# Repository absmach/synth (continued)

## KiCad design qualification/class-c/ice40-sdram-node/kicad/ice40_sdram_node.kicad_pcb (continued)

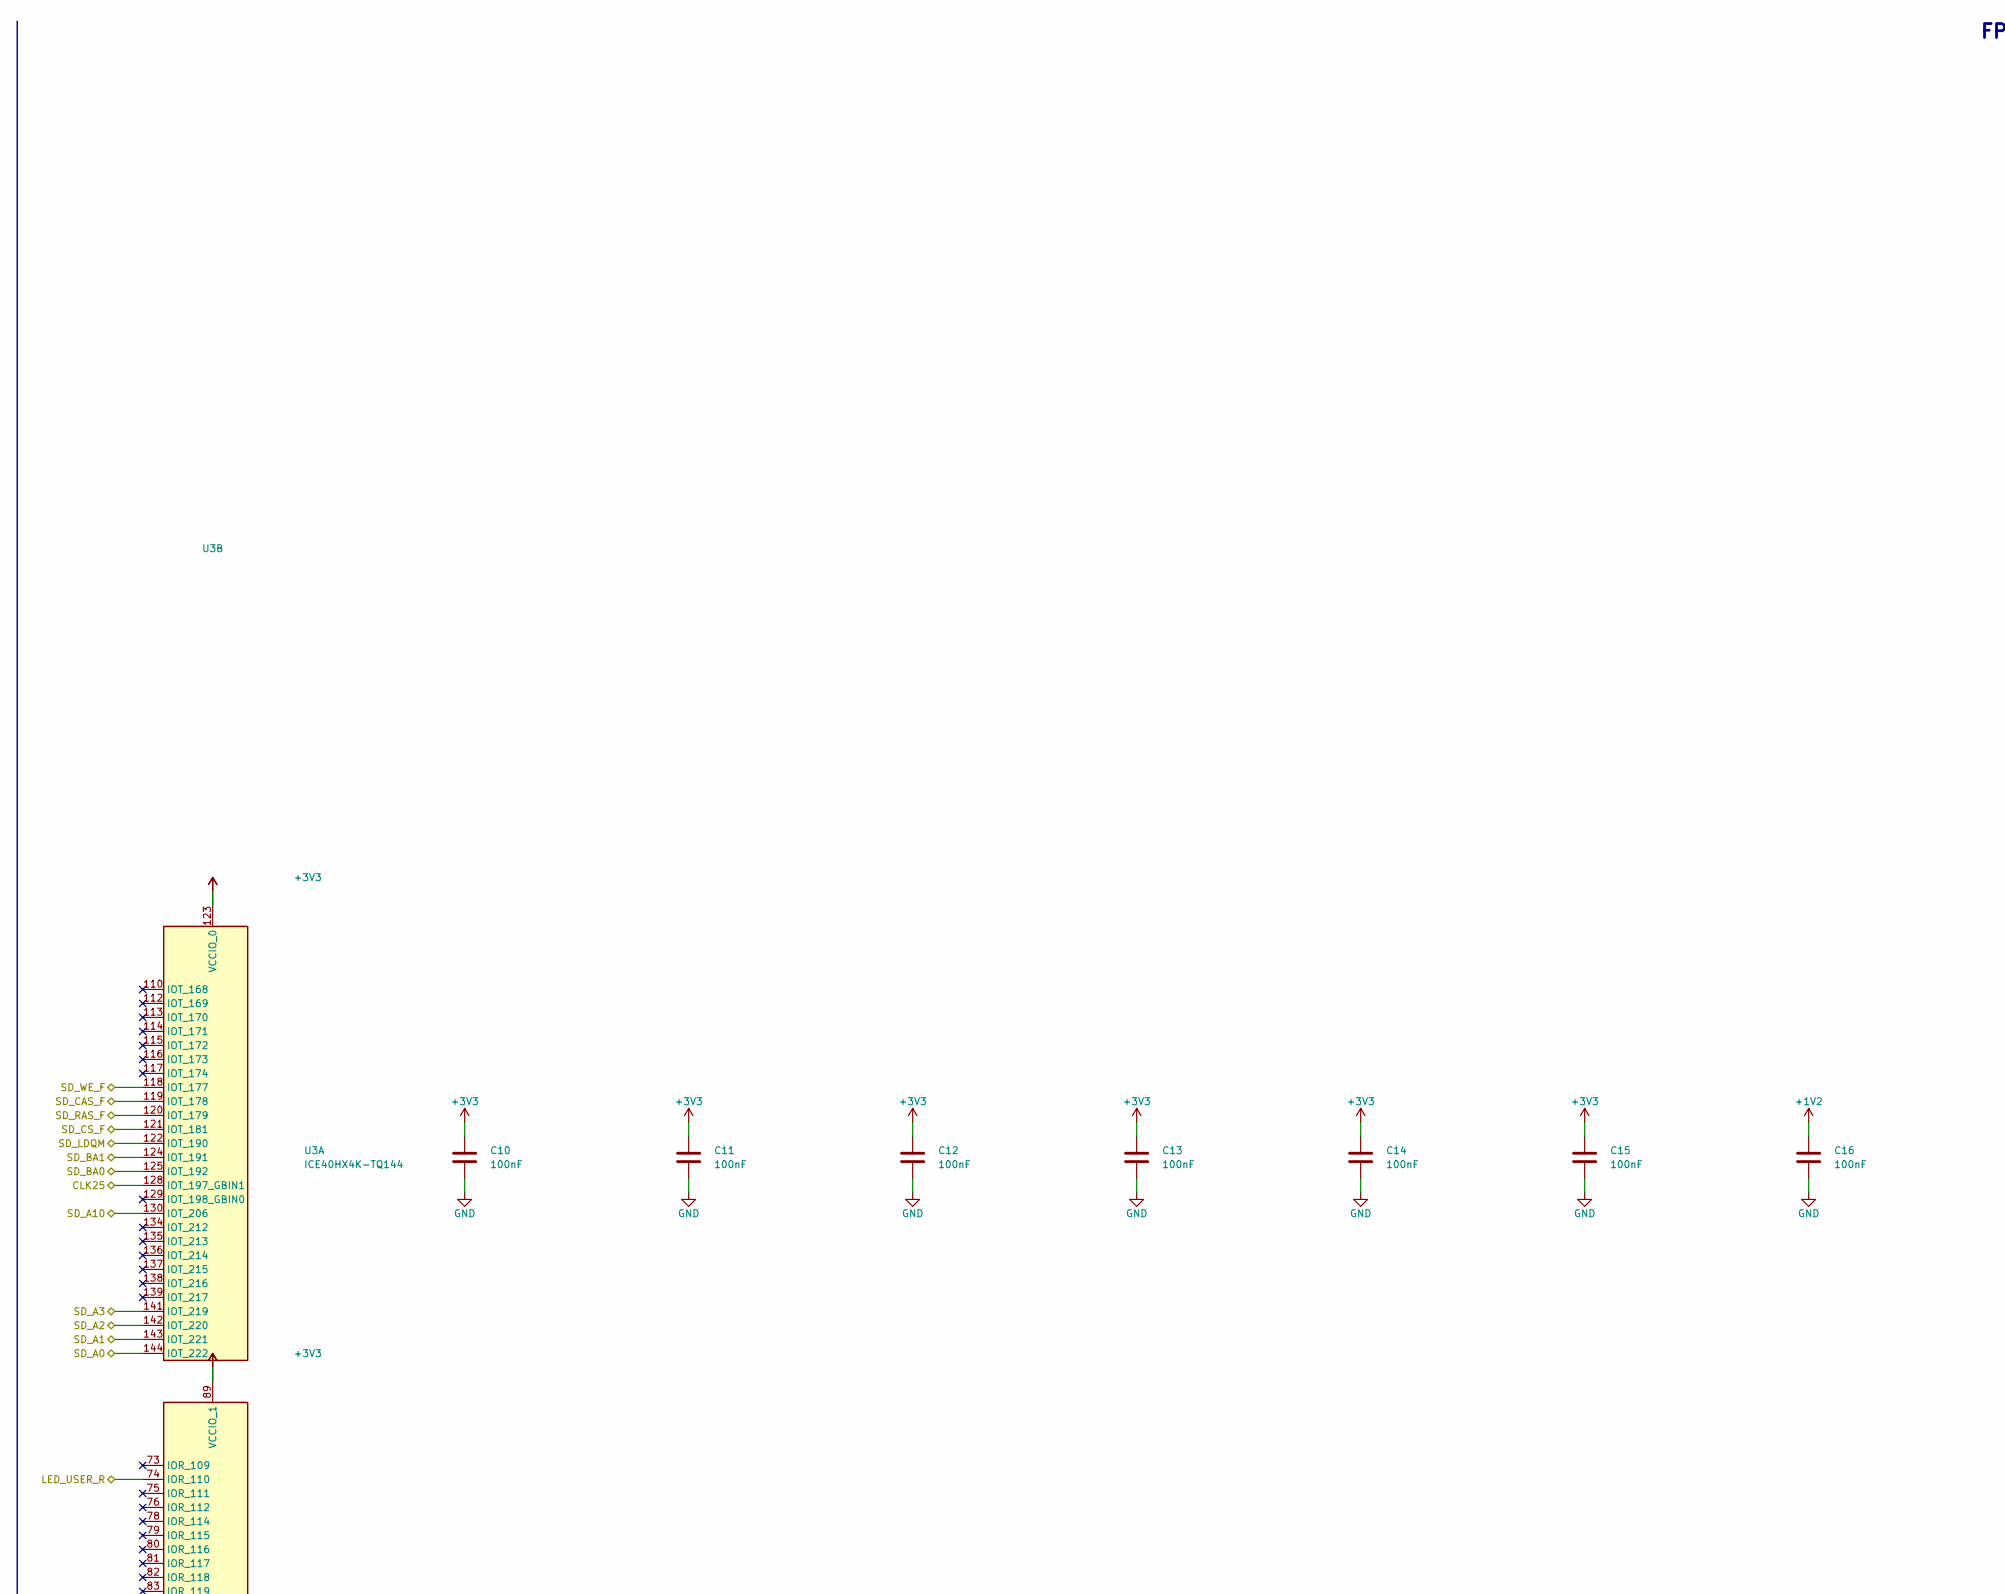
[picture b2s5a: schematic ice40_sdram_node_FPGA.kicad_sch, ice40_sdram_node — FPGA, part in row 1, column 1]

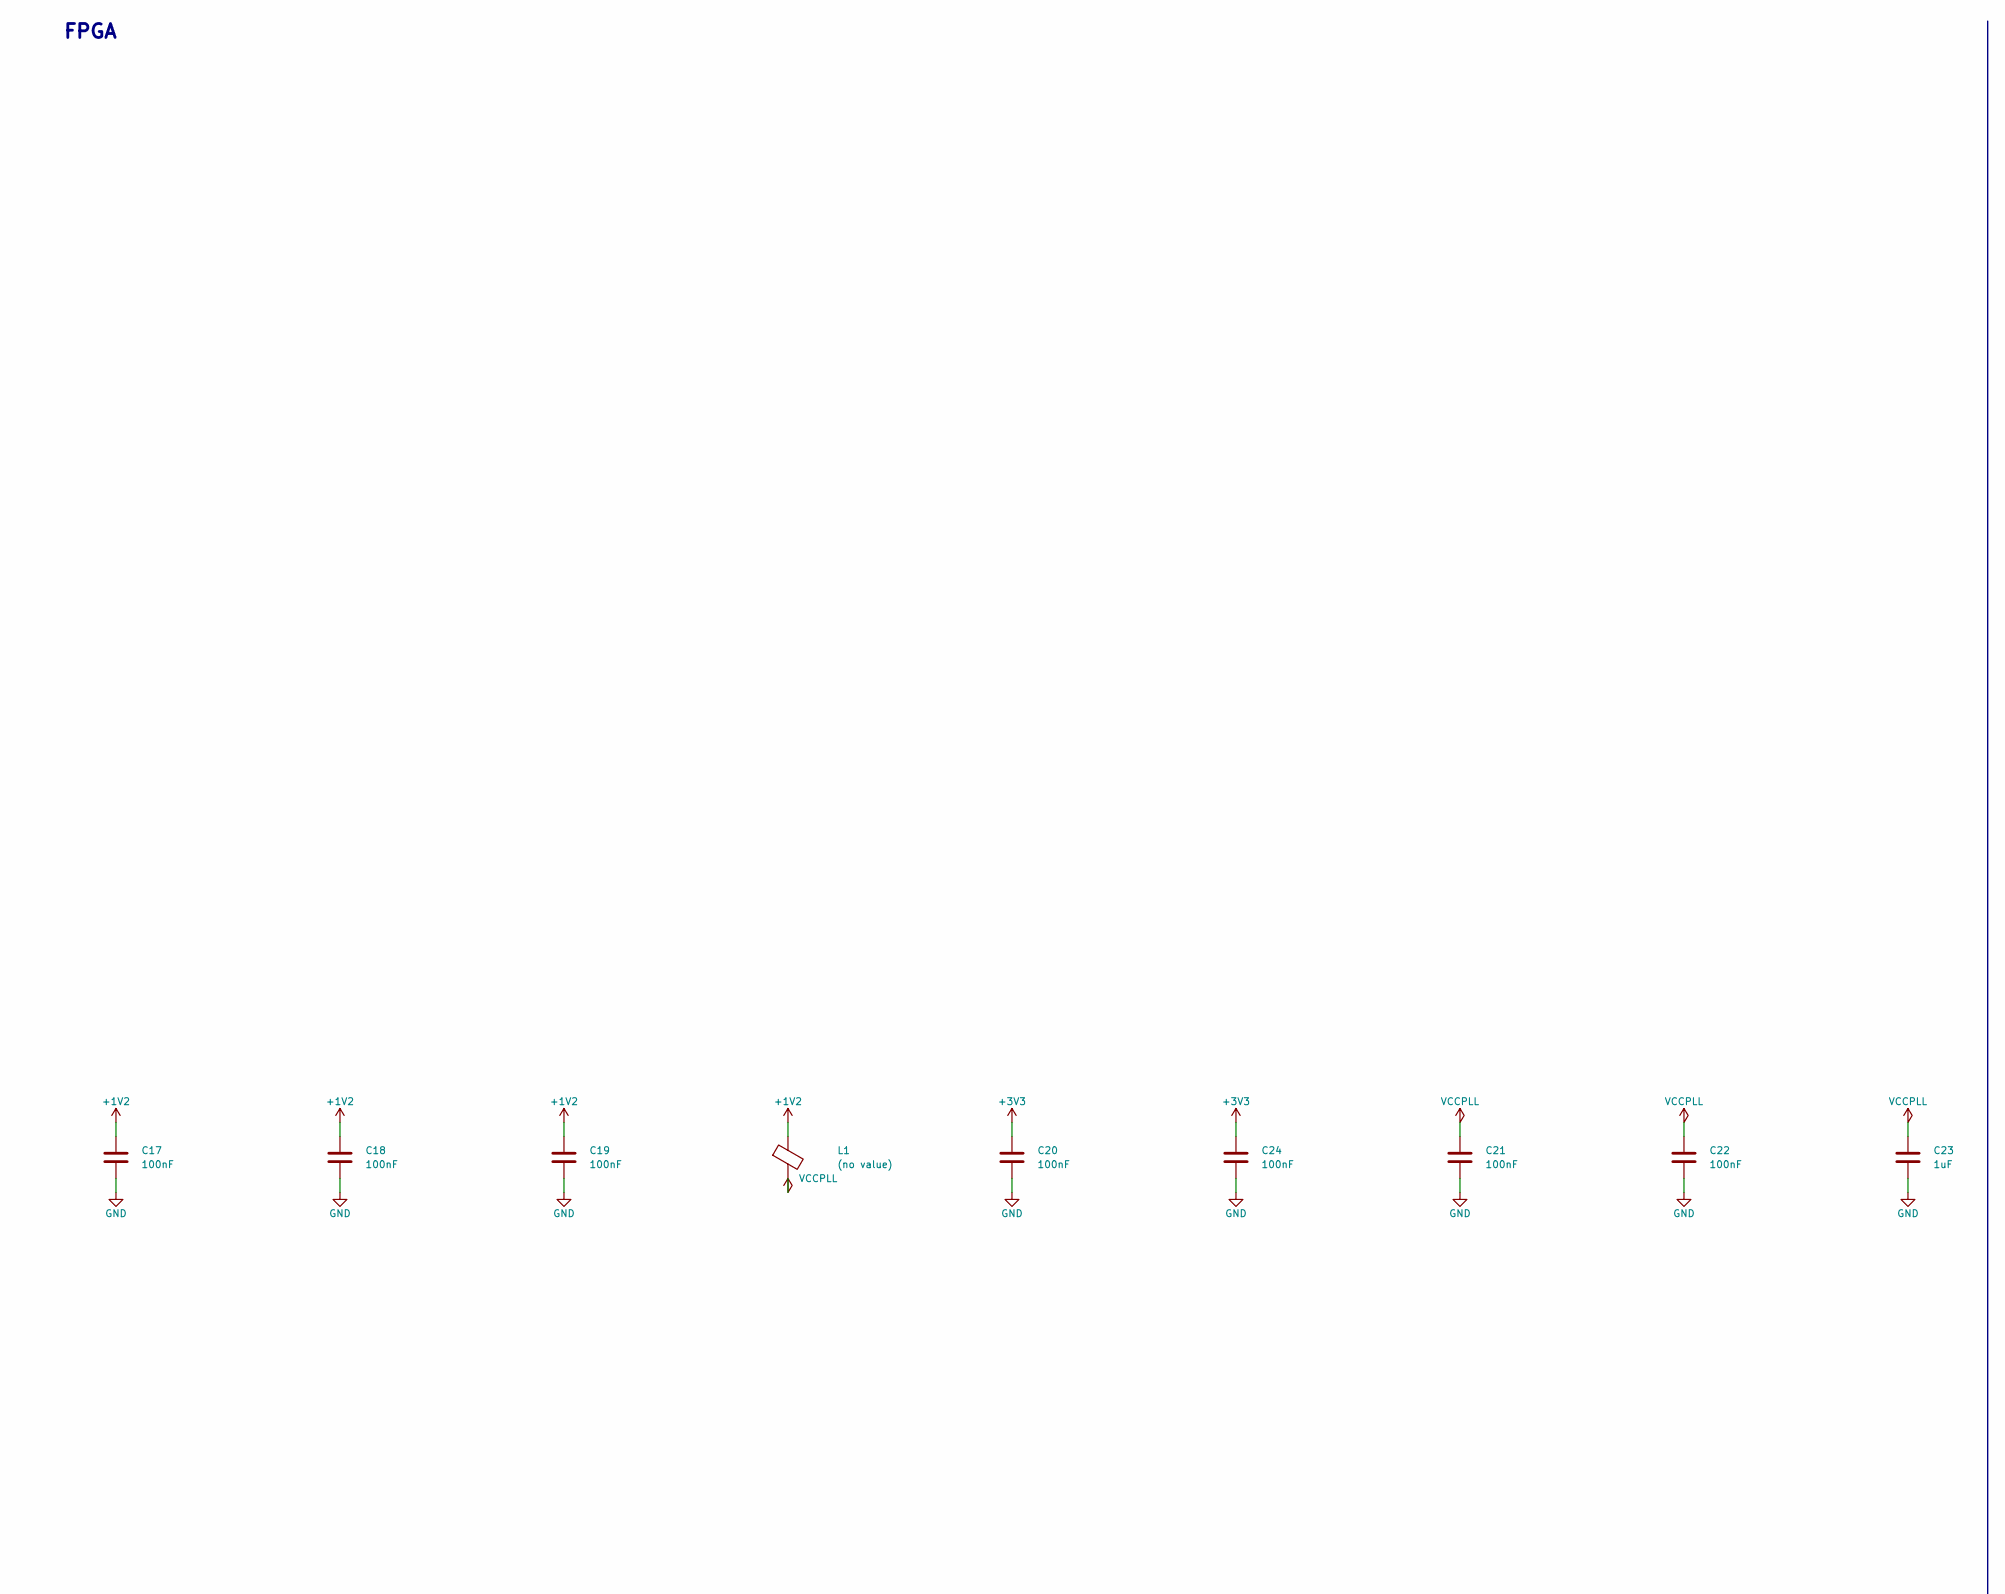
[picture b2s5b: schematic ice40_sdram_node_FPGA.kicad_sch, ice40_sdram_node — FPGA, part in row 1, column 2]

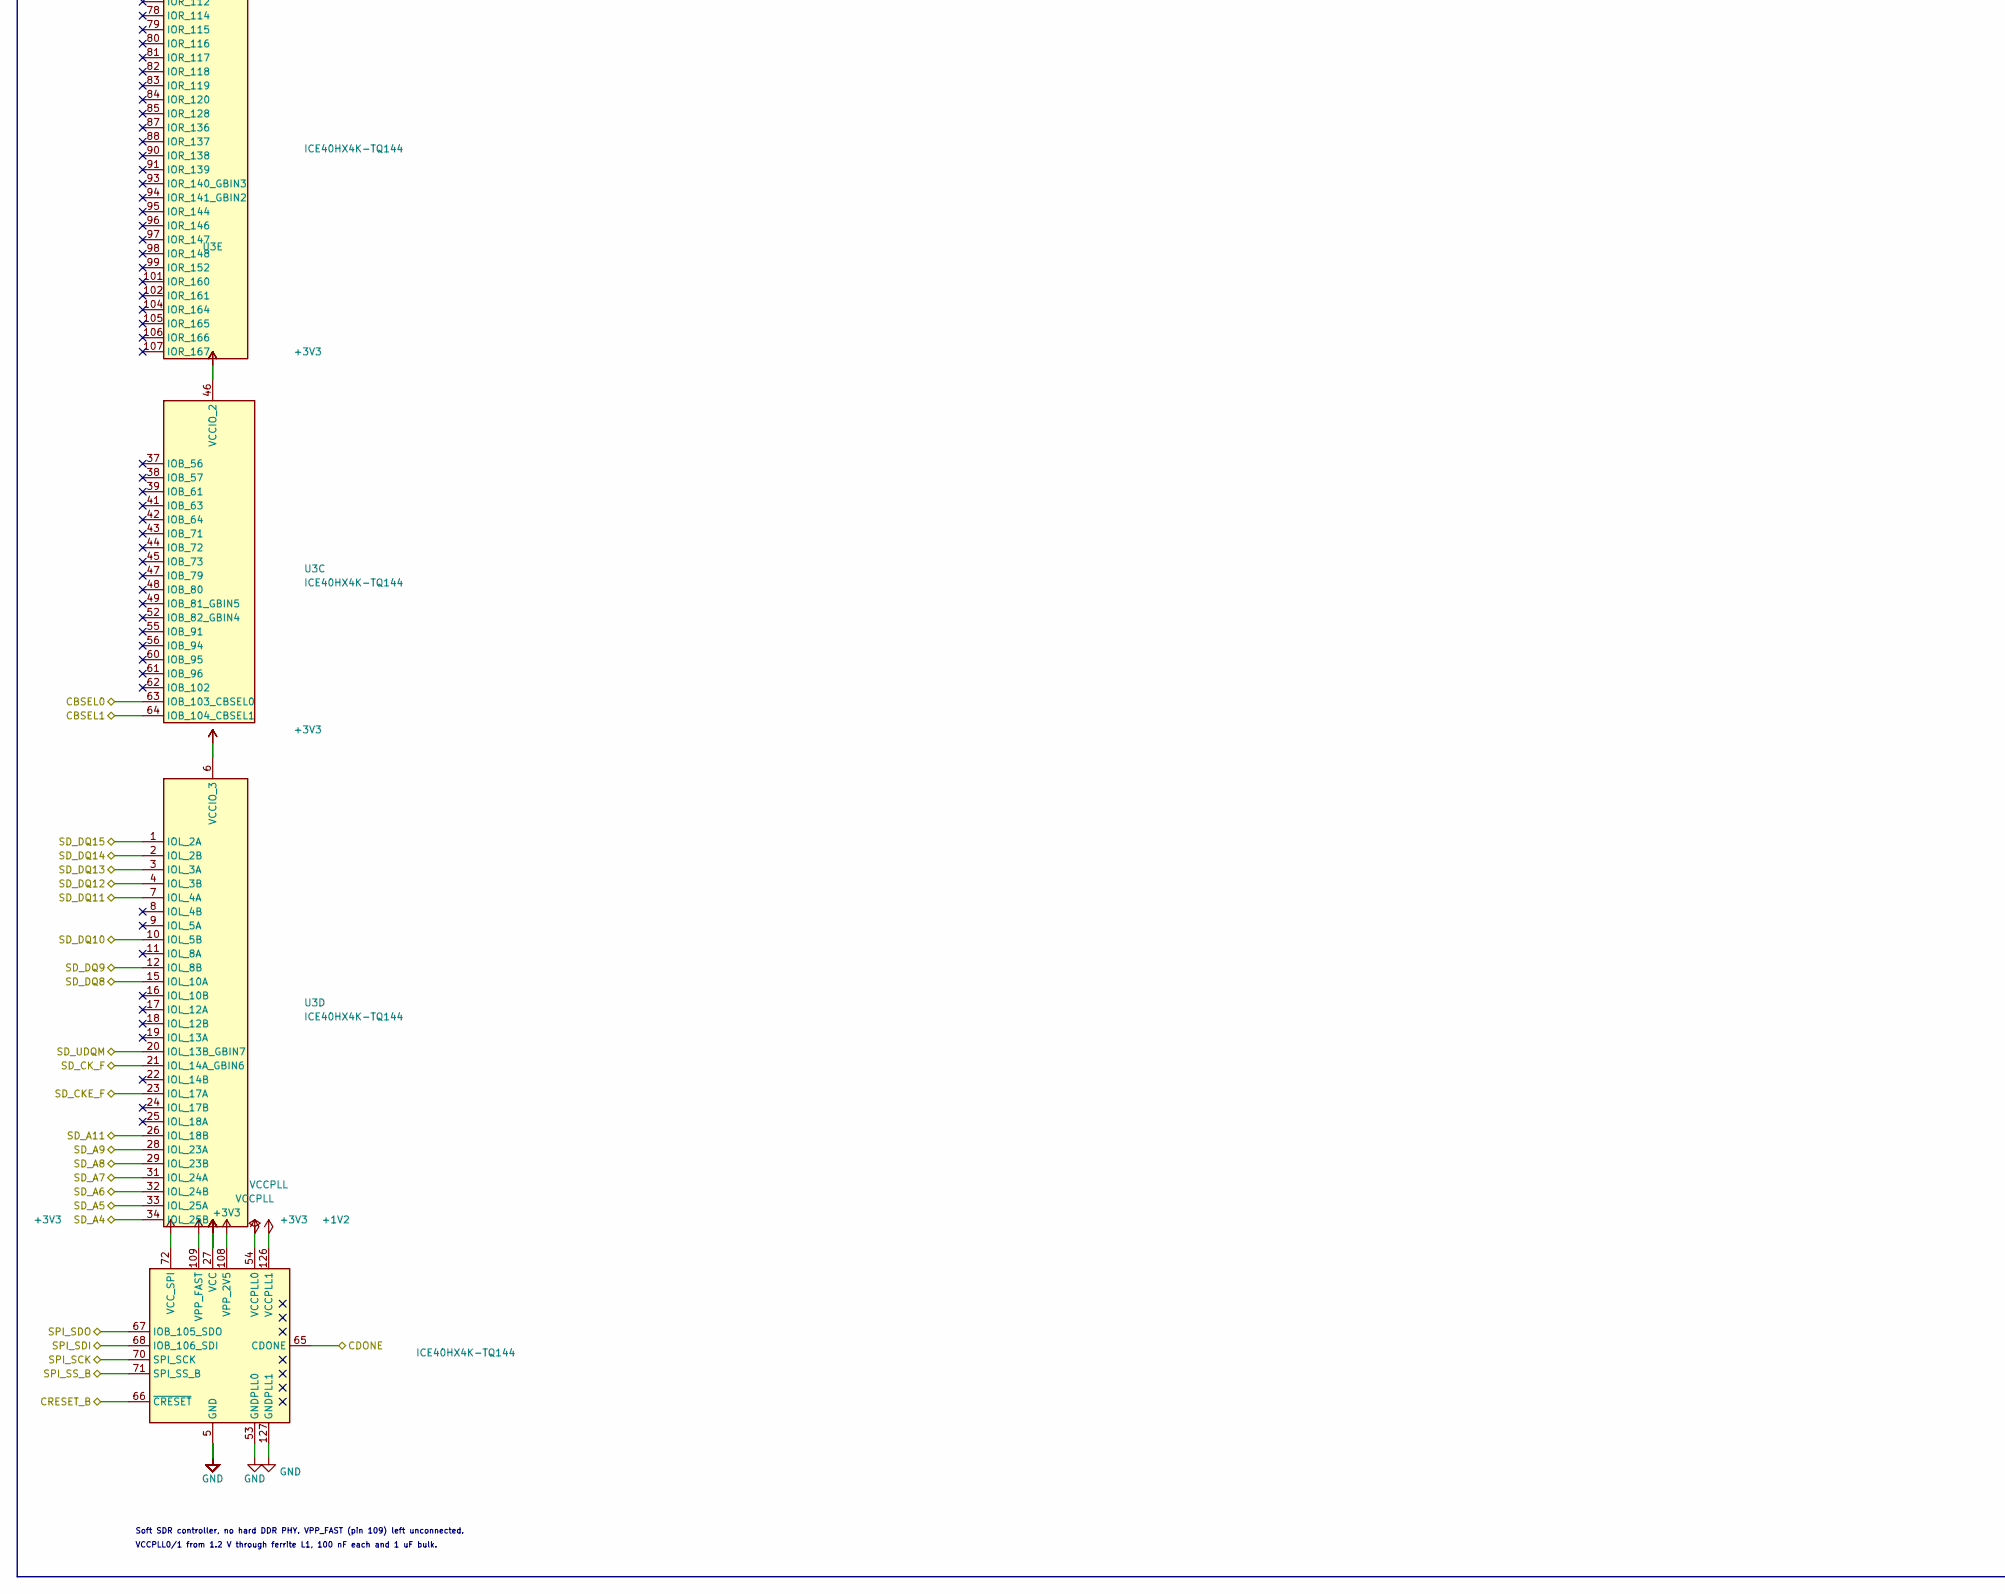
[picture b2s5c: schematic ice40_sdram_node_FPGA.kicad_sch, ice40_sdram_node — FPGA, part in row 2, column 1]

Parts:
C10, C11, C12, C13, C14, C15, C16, C17, C18, C19, C20, C21, C22, C24: 100nF; C_0402_1005Metric
C23: 1uF; C_0603_1608Metric
L1: (no value); L_0603_1608Metric
U3: ICE40HX4K-TQ144; TQFP-144_20x20mm_P0.5mm; MPN ICE40HX4K-TQ144; LCSC C1521989

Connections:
+1V2: C16.1, C17.1, C18.1, C19.1, L1.1, U3.27 (VCC), U3.40 (VCC), U3.92 (VCC), U3.111 (VCC); also elsewhere on the board
+3V3: C10.1, C11.1, C12.1, C13.1, C14.1, C15.1, C20.1, C24.1, U3.6 (VCCIO_3), U3.30 (VCCIO_3), U3.46 (VCCIO_2), U3.57 (VCCIO_2), U3.72 (VCC_SPI), U3.89 (VCCIO_1), U3.100 (VCCIO_1), U3.108 (VPP_2V5), U3.109 (VPP_FAST), U3.123 (VCCIO_0), U3.131 (VCCIO_0); also elsewhere on the board
CBSEL0: U3.63 (IOB_103_CBSEL0); also elsewhere on the board
CBSEL1: U3.64 (IOB_104_CBSEL1); also elsewhere on the board
CDONE: U3.65 (CDONE); also elsewhere on the board
CLK25: U3.128 (IOT_197_GBIN1); also elsewhere on the board
CRESET_B: U3.66 (~CRESET); also elsewhere on the board
GND: C10.2, C11.2, C12.2, C13.2, C14.2, C15.2, C16.2, C17.2, C18.2, C19.2, C20.2, C21.2, C22.2, C23.2, C24.2, U3.5 (GND), U3.13 (GND), U3.14 (GND), U3.53 (GNDPLL0), U3.59 (GND), U3.69 (GND), U3.86 (GND), U3.103 (GND), U3.127 (GNDPLL1), U3.132 (GND), U3.140 (GND); also elsewhere on the board
LED_USER_R: U3.74 (IOR_110); also elsewhere on the board
SD_A0: U3.144 (IOT_222); also elsewhere on the board
SD_A1: U3.143 (IOT_221); also elsewhere on the board
SD_A2: U3.142 (IOT_220); also elsewhere on the board
SD_A3: U3.141 (IOT_219); also elsewhere on the board
SD_A4: U3.34 (IOL_25B); also elsewhere on the board
SD_A5: U3.33 (IOL_25A); also elsewhere on the board
SD_A6: U3.32 (IOL_24B); also elsewhere on the board
SD_A7: U3.31 (IOL_24A); also elsewhere on the board
SD_A8: U3.29 (IOL_23B); also elsewhere on the board
SD_A9: U3.28 (IOL_23A); also elsewhere on the board
SD_A10: U3.130 (IOT_206); also elsewhere on the board
SD_A11: U3.26 (IOL_18B); also elsewhere on the board
SD_BA0: U3.125 (IOT_192); also elsewhere on the board
SD_BA1: U3.124 (IOT_191); also elsewhere on the board
SD_CAS_F: U3.119 (IOT_178); also elsewhere on the board
SD_CKE_F: U3.23 (IOL_17A); also elsewhere on the board
SD_CK_F: U3.21 (IOL_14A_GBIN6); also elsewhere on the board
SD_CS_F: U3.121 (IOT_181); also elsewhere on the board
SD_DQ8: U3.15 (IOL_10A); also elsewhere on the board
SD_DQ9: U3.12 (IOL_8B); also elsewhere on the board
SD_DQ10: U3.10 (IOL_5B); also elsewhere on the board
SD_DQ11: U3.7 (IOL_4A); also elsewhere on the board
SD_DQ12: U3.4 (IOL_3B); also elsewhere on the board
SD_DQ13: U3.3 (IOL_3A); also elsewhere on the board
SD_DQ14: U3.2 (IOL_2B); also elsewhere on the board
SD_DQ15: U3.1 (IOL_2A); also elsewhere on the board
SD_LDQM: U3.122 (IOT_190); also elsewhere on the board
SD_RAS_F: U3.120 (IOT_179); also elsewhere on the board
SD_UDQM: U3.20 (IOL_13B_GBIN7); also elsewhere on the board
SD_WE_F: U3.118 (IOT_177); also elsewhere on the board
SPI_SCK: U3.70 (IOB_107_SCK); also elsewhere on the board
SPI_SDI: U3.68 (IOB_106_SDI); also elsewhere on the board
SPI_SDO: U3.67 (IOB_105_SDO); also elsewhere on the board
SPI_SS_B: U3.71 (IOB_108_SS); also elsewhere on the board
VCCPLL: C21.1, C22.1, C23.1, L1.2, U3.54 (VCCPLL0), U3.126 (VCCPLL1)

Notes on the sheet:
FPGA
Soft SDR controller, no hard DDR PHY. VPP_FAST (pin 109) left unconnected.
VCCPLL0/1 from 1.2 V through ferrite L1, 100 nF each and 1 uF bulk.

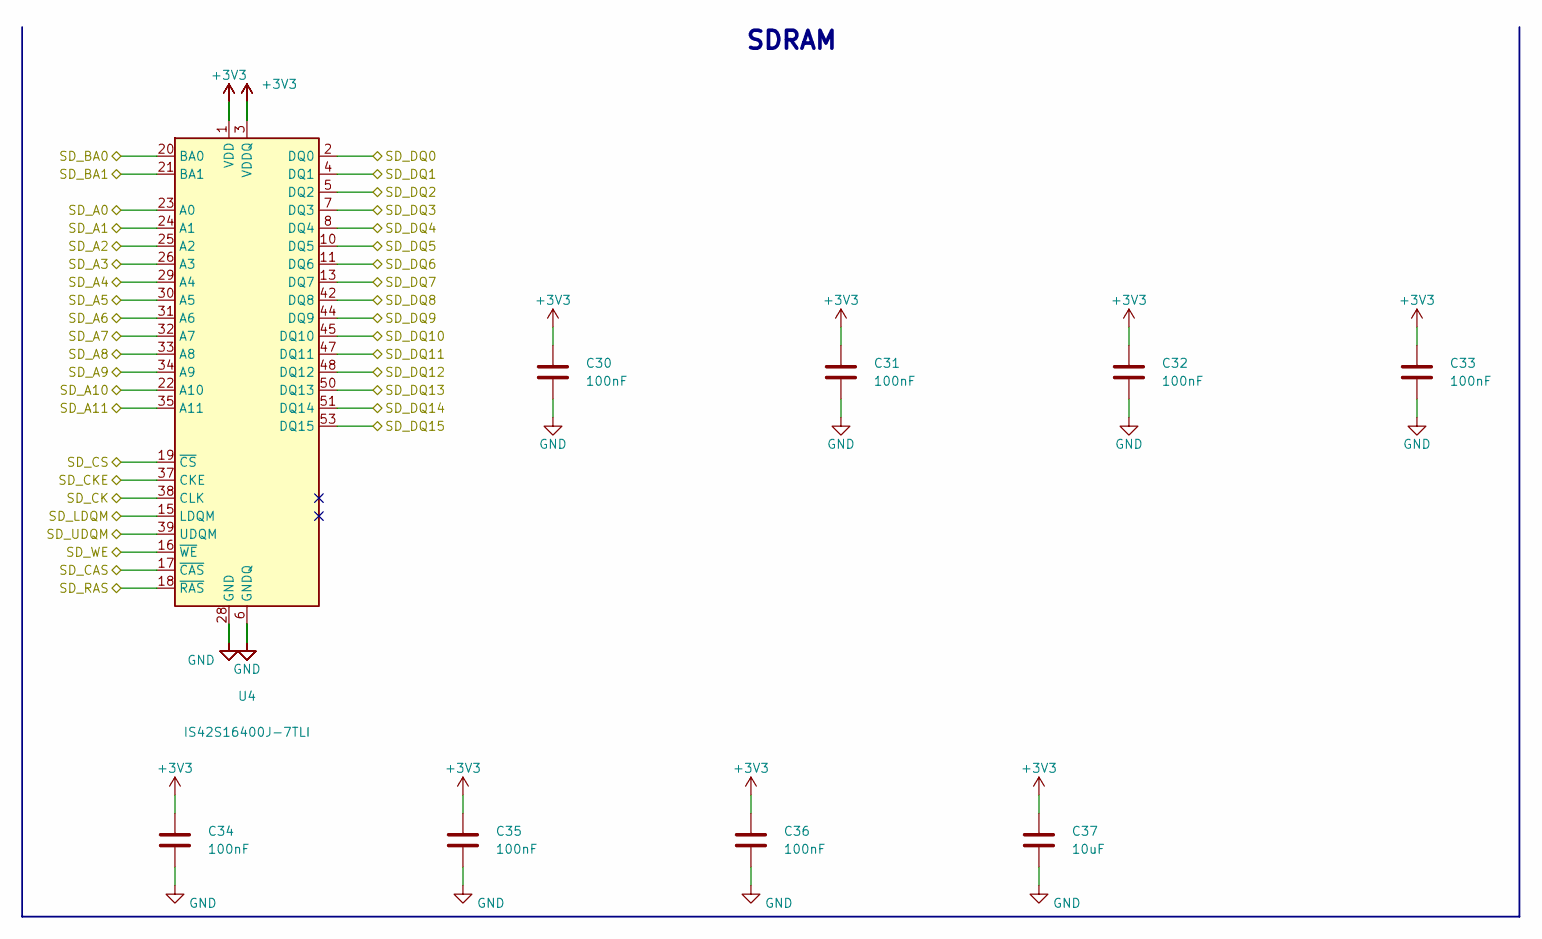
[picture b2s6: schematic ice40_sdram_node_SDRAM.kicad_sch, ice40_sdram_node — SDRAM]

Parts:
C30, C31, C32, C33, C34, C35, C36: 100nF; C_0402_1005Metric
C37: 10uF; C_0805_2012Metric
U4: IS42S16400J-7TLI; TSOP-II-54_22.2x10.16mm_P0.8mm; MPN IS42S16400J-7TLI; LCSC C2979137

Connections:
+3V3: C30.1, C31.1, C32.1, C33.1, C34.1, C35.1, C36.1, C37.1, U4.1 (VDD), U4.3 (VDDQ), U4.9 (VDDQ), U4.14 (VDD), U4.27 (VDD), U4.43 (VDDQ), U4.49 (VDDQ); also elsewhere on the board
GND: C30.2, C31.2, C32.2, C33.2, C34.2, C35.2, C36.2, C37.2, U4.6 (GNDQ), U4.12 (GNDQ), U4.28 (GND), U4.41 (GND), U4.46 (GNDQ), U4.52 (GNDQ), U4.54 (GND); also elsewhere on the board
SD_A0: U4.23 (A0); also elsewhere on the board
SD_A1: U4.24 (A1); also elsewhere on the board
SD_A2: U4.25 (A2); also elsewhere on the board
SD_A3: U4.26 (A3); also elsewhere on the board
SD_A4: U4.29 (A4); also elsewhere on the board
SD_A5: U4.30 (A5); also elsewhere on the board
SD_A6: U4.31 (A6); also elsewhere on the board
SD_A7: U4.32 (A7); also elsewhere on the board
SD_A8: U4.33 (A8); also elsewhere on the board
SD_A9: U4.34 (A9); also elsewhere on the board
SD_A10: U4.22 (A10); also elsewhere on the board
SD_A11: U4.35 (A11); also elsewhere on the board
SD_BA0: U4.20 (BA0); also elsewhere on the board
SD_BA1: U4.21 (BA1); also elsewhere on the board
SD_CAS: U4.17 (~CAS); also elsewhere on the board
SD_CK: U4.38 (CLK); also elsewhere on the board
SD_CKE: U4.37 (CKE); also elsewhere on the board
SD_CS: U4.19 (~CS); also elsewhere on the board
SD_DQ0: U4.2 (DQ0); also elsewhere on the board
SD_DQ1: U4.4 (DQ1); also elsewhere on the board
SD_DQ2: U4.5 (DQ2); also elsewhere on the board
SD_DQ3: U4.7 (DQ3); also elsewhere on the board
SD_DQ4: U4.8 (DQ4); also elsewhere on the board
SD_DQ5: U4.10 (DQ5); also elsewhere on the board
SD_DQ6: U4.11 (DQ6); also elsewhere on the board
SD_DQ7: U4.13 (DQ7); also elsewhere on the board
SD_DQ8: U4.42 (DQ8); also elsewhere on the board
SD_DQ9: U4.44 (DQ9); also elsewhere on the board
SD_DQ10: U4.45 (DQ10); also elsewhere on the board
SD_DQ11: U4.47 (DQ11); also elsewhere on the board
SD_DQ12: U4.48 (DQ12); also elsewhere on the board
SD_DQ13: U4.50 (DQ13); also elsewhere on the board
SD_DQ14: U4.51 (DQ14); also elsewhere on the board
SD_DQ15: U4.53 (DQ15); also elsewhere on the board
SD_LDQM: U4.15 (LDQM); also elsewhere on the board
SD_RAS: U4.18 (~RAS); also elsewhere on the board
SD_UDQM: U4.39 (UDQM); also elsewhere on the board
SD_WE: U4.16 (~WE); also elsewhere on the board

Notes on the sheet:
SDRAM

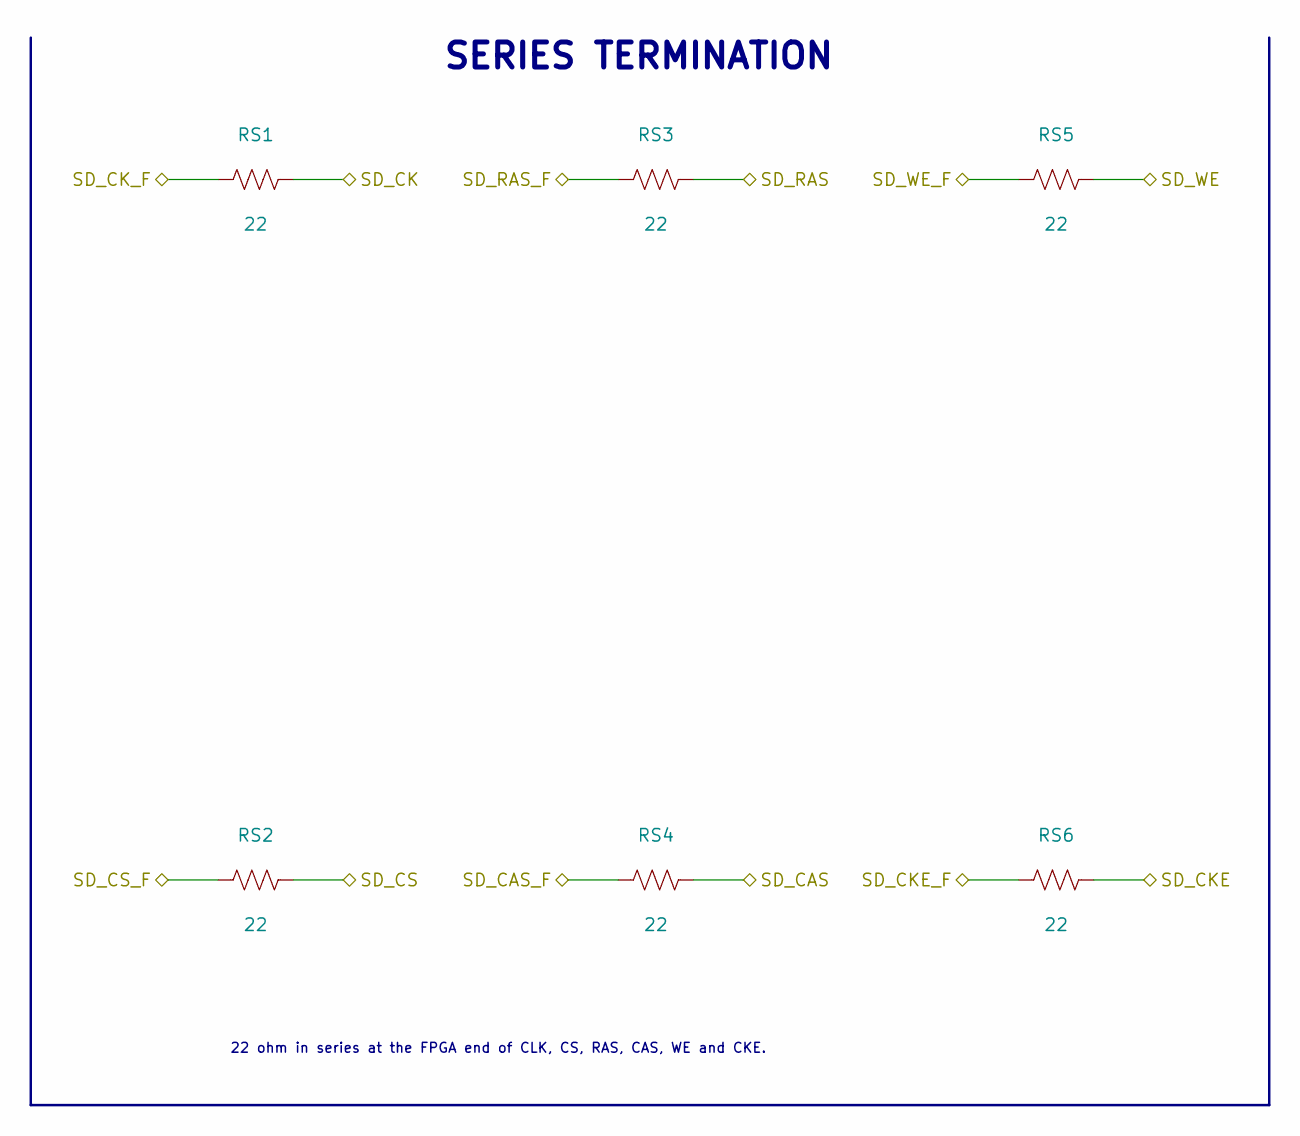
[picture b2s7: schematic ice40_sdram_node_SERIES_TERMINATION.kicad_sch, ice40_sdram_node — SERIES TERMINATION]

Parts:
RS1, RS2, RS3, RS4, RS5, RS6: 22; R_0402_1005Metric

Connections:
SD_CAS: RS4.2; also elsewhere on the board
SD_CAS_F: RS4.1; also elsewhere on the board
SD_CK: RS1.2; also elsewhere on the board
SD_CKE: RS6.2; also elsewhere on the board
SD_CKE_F: RS6.1; also elsewhere on the board
SD_CK_F: RS1.1; also elsewhere on the board
SD_CS: RS2.2; also elsewhere on the board
SD_CS_F: RS2.1; also elsewhere on the board
SD_RAS: RS3.2; also elsewhere on the board
SD_RAS_F: RS3.1; also elsewhere on the board
SD_WE: RS5.2; also elsewhere on the board
SD_WE_F: RS5.1; also elsewhere on the board

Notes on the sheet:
SERIES TERMINATION
22 ohm in series at the FPGA end of CLK, CS, RAS, CAS, WE and CKE.

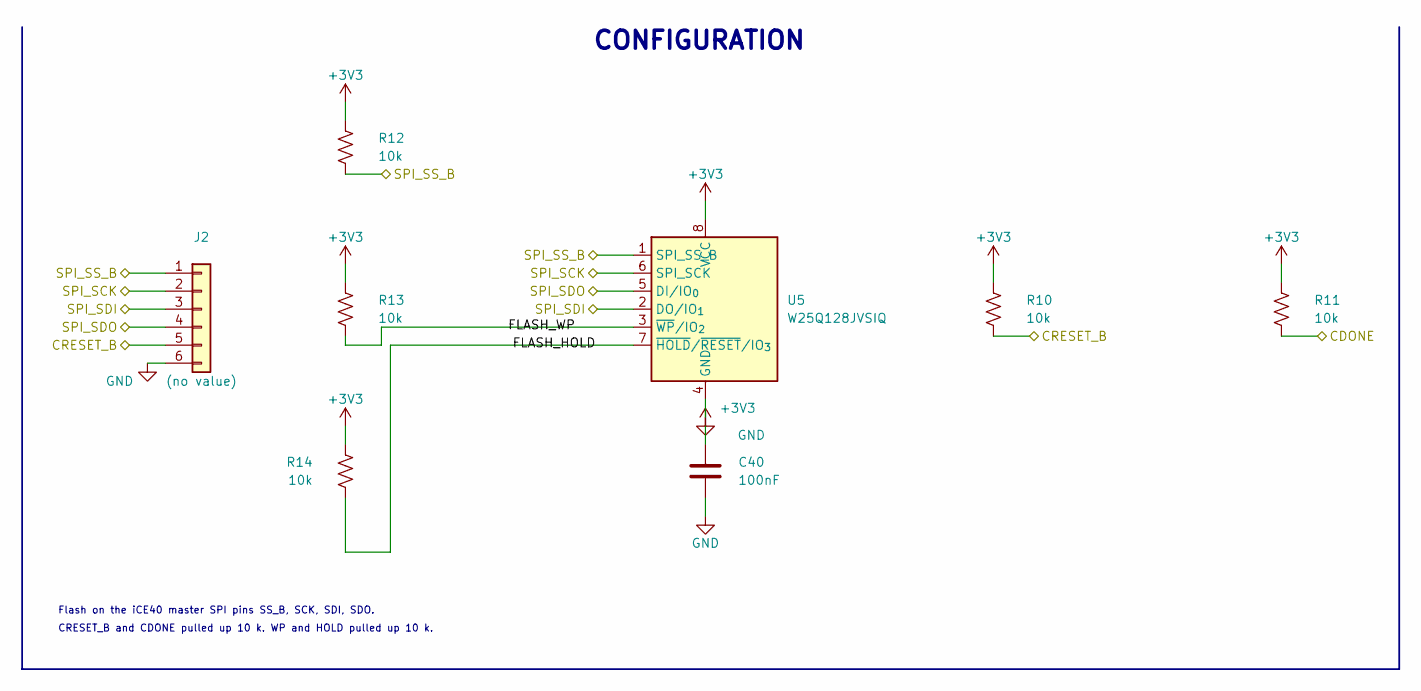
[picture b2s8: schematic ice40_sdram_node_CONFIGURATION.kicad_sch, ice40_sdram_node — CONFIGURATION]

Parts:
C40: 100nF; C_0603_1608Metric
J2: (no value); PinHeader_1x06_P2.54mm_Vertical
R10, R11, R12, R13, R14: 10k; R_0603_1608Metric
U5: W25Q128JVSIQ; SOIC-8_5.3x5.3mm_P1.27mm; MPN W25Q128JVSIQ; LCSC C97521

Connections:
+3V3: C40.1, R10.1, R11.1, R12.1, R13.1, R14.1, U5.8 (VCC); also elsewhere on the board
CDONE: R11.2; also elsewhere on the board
CRESET_B: J2.5, R10.2; also elsewhere on the board
FLASH_HOLD: R14.2, U5.7 (~HOLD/~RESET/IO_{3})
FLASH_WP: R13.2, U5.3 (~WP/IO_{2})
GND: C40.2, J2.6, U5.4 (GND); also elsewhere on the board
SPI_SCK: J2.2, U5.6 (CLK); also elsewhere on the board
SPI_SDI: J2.3, U5.2 (DO/IO_{1}); also elsewhere on the board
SPI_SDO: J2.4, U5.5 (DI/IO_{0}); also elsewhere on the board
SPI_SS_B: J2.1, R12.2, U5.1 (~CS); also elsewhere on the board

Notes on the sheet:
CONFIGURATION
Flash on the iCE40 master SPI pins SS_B, SCK, SDI, SDO.
CRESET_B and CDONE pulled up 10 k. WP and HOLD pulled up 10 k.

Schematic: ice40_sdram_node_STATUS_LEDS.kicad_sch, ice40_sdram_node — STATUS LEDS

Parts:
D2: 0603-RED; LED_0603_1608Metric; MPN 0603-RED; LCSC C2286
D3, D4: 0603-GREEN; LED_0603_1608Metric; MPN 0603-GREEN; LCSC C72043
Q2: AO3400A; SOT-23; MPN AO3400A
R20, R21, R22: 1k; R_0603_1608Metric

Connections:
+3V3: R20.1, R21.1; also elsewhere on the board
CDONE: Q2.1 (G); also elsewhere on the board
GND: D2.1 (K), D4.1 (K), Q2.2 (S); also elsewhere on the board
LED_DONE_A: D3.2 (A), R21.2
LED_DONE_K: D3.1 (K), Q2.3 (D)
LED_PWR: D2.2 (A), R20.2
LED_USER_A: D4.2 (A), R22.2
LED_USER_R: R22.1; also elsewhere on the board

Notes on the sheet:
STATUS LEDS
D2 3.3 V present. D3 lit when CDONE is high (Q2 buffers the open-drain pin). D4 user LED.

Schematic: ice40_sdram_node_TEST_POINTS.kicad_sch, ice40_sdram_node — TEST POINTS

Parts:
TP1, TP2, TP3, TP4, TP5, TP6, TP7: (no value); TestPoint_Pad_D1.5mm

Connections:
+1V2: TP3.1; also elsewhere on the board
+3V3: TP2.1; also elsewhere on the board
+5V: TP1.1; also elsewhere on the board
CDONE: TP5.1; also elsewhere on the board
CRESET_B: TP6.1; also elsewhere on the board
GND: TP4.1, TP7.1; also elsewhere on the board

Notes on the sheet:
TEST POINTS

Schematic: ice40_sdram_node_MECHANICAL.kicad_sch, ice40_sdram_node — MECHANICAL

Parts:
H1, H2: (no value); MountingHole_2.5mm

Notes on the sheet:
MECHANICAL

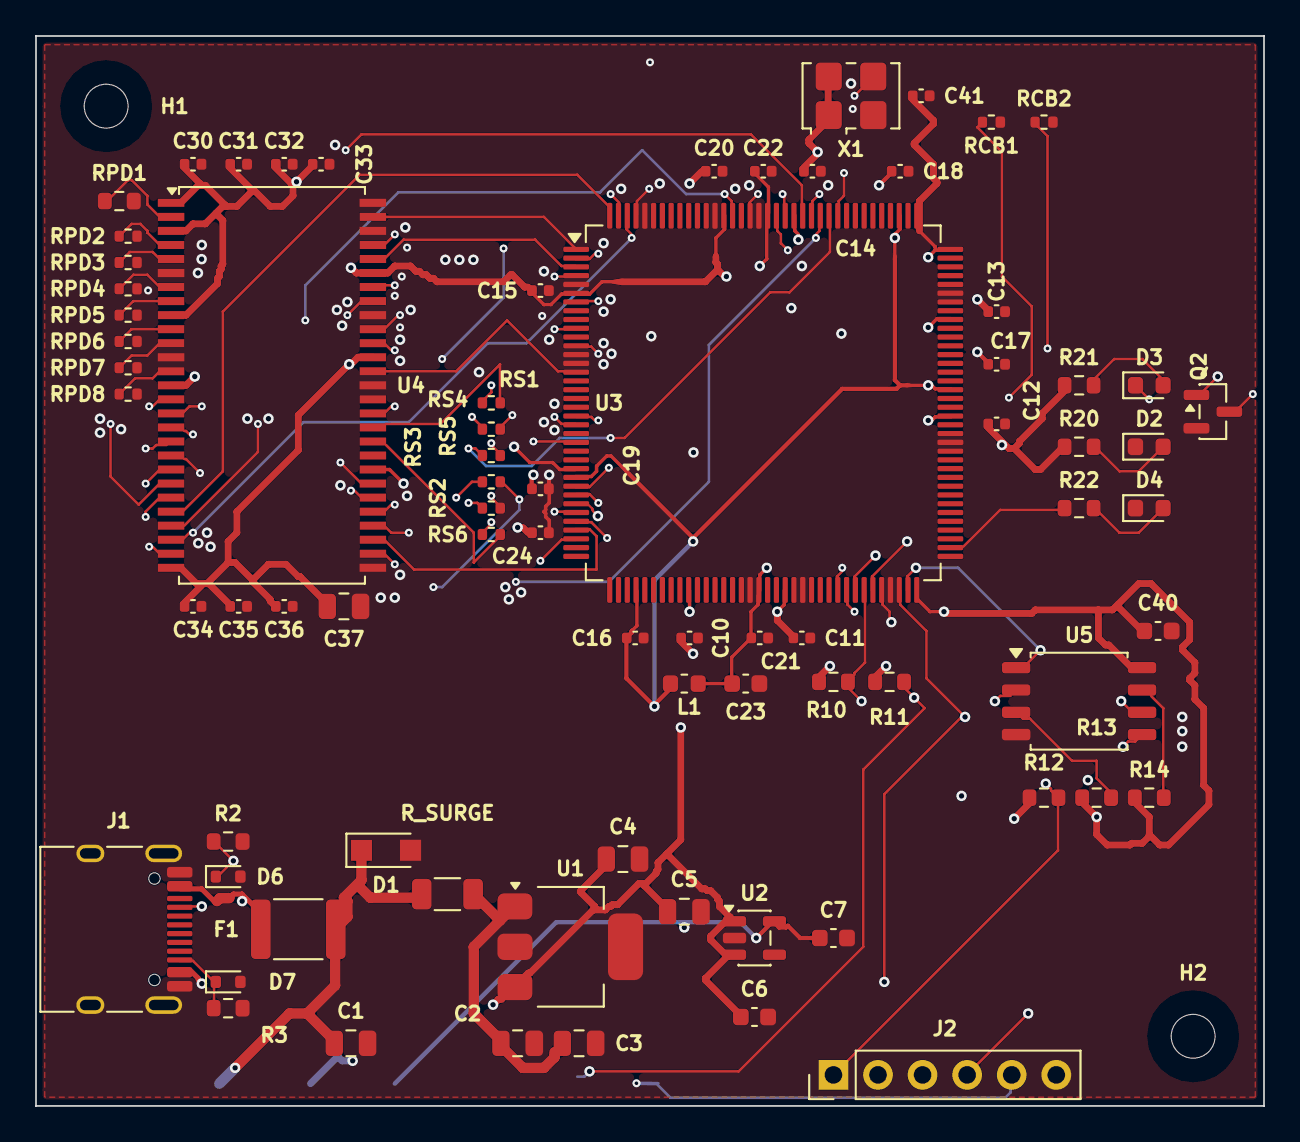
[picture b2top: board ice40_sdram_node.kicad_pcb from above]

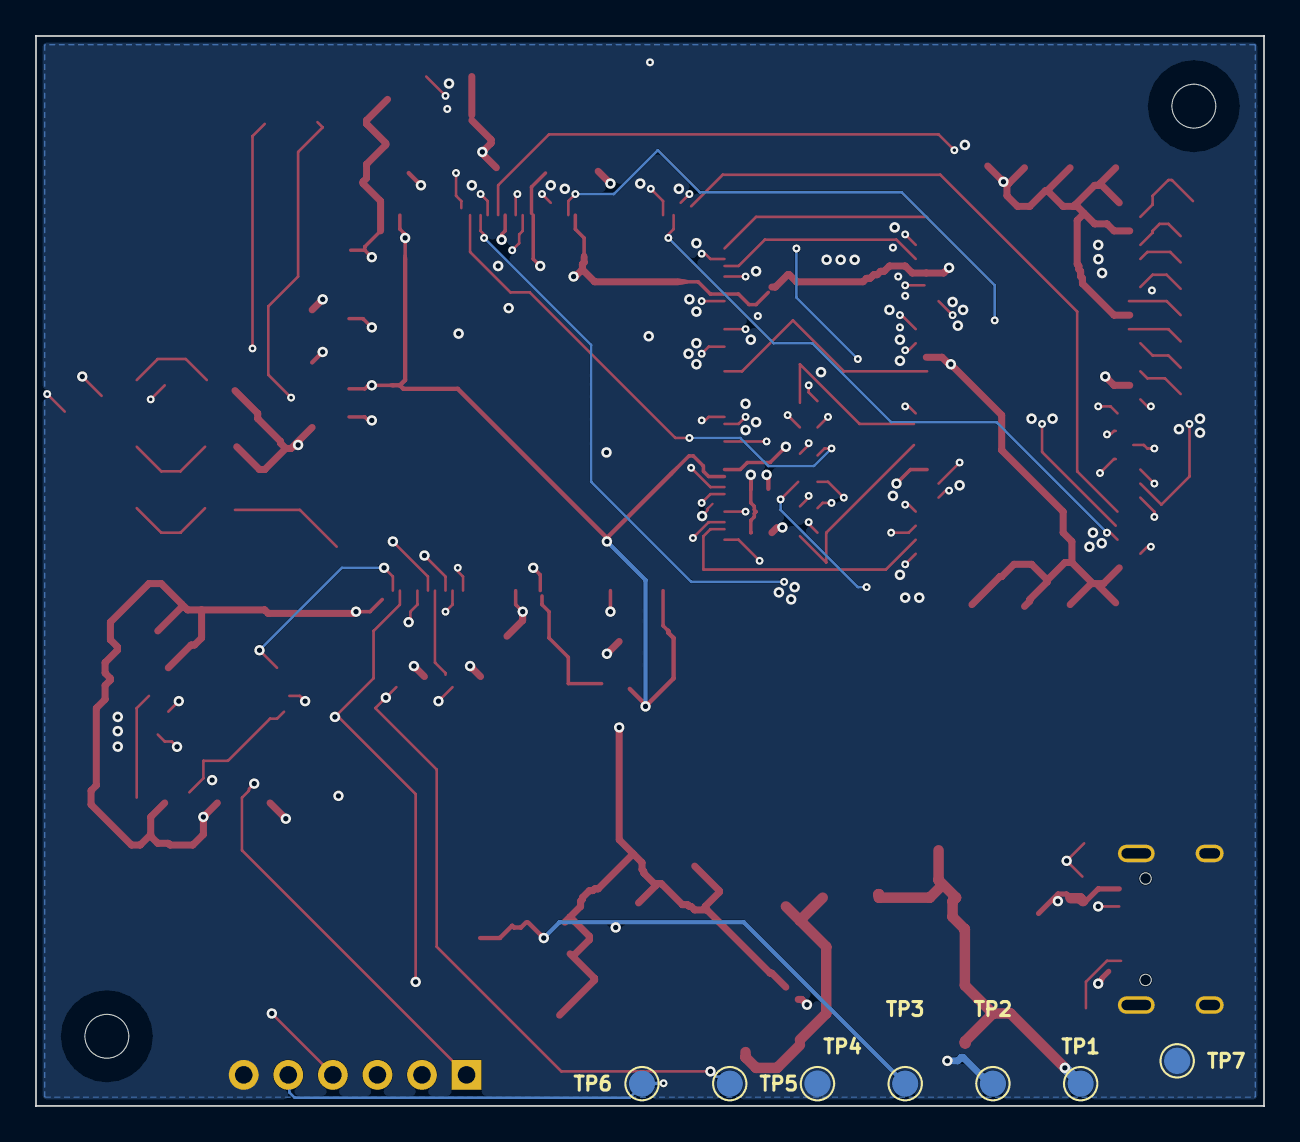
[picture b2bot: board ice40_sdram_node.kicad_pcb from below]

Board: 6 copper layers, 70.0 x 61.0 mm, 85 parts (7 on the bottom side), 69 nets.
